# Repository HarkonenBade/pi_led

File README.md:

# pi_led
Raspberry Pi LED Driver

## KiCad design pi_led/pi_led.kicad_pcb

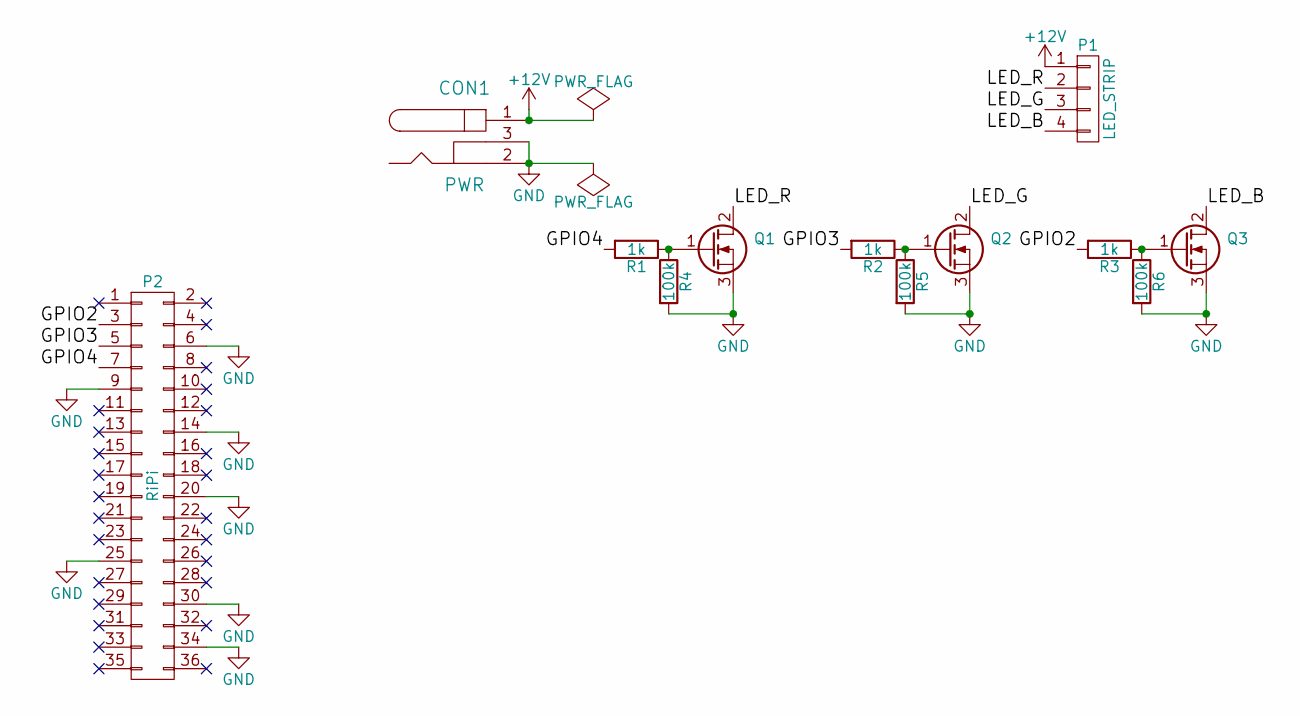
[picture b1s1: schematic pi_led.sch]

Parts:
CON1: PWR; barrel_jack
P1: LED_STRIP; Pin_Header_Angled_1x04
P2: RiPi; Pin_Header_Straight_2x18
Q1, Q2, Q3: STP16NF06L; TO-220_Neutral123_Horizontal; Farnell SC11129
R1, R2, R3: 1k; Resistor_Horizontal_RM10mm
R4, R5, R6: 100k; Resistor_Horizontal_RM10mm

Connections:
+12V: CON1.1, P1.1
/GPIO2: P2.3, R3.2
/GPIO3: P2.5, R2.2
/GPIO4: P2.7, R1.2
/LED_B: P1.4, Q3.2 (D)
/LED_G: P1.3, Q2.2 (D)
/LED_R: P1.2, Q1.2 (D)
GND: CON1.2, CON1.3, P2.6, P2.9, P2.14, P2.20, P2.25, P2.30, P2.34, Q1.3 (S), Q2.3 (S), Q3.3 (S), R4.2, R5.2, R6.2
unnamed: Q1.1 (G), R1.1, R4.1
unnamed: Q2.1 (G), R2.1, R5.1
unnamed: Q3.1 (G), R3.1, R6.1

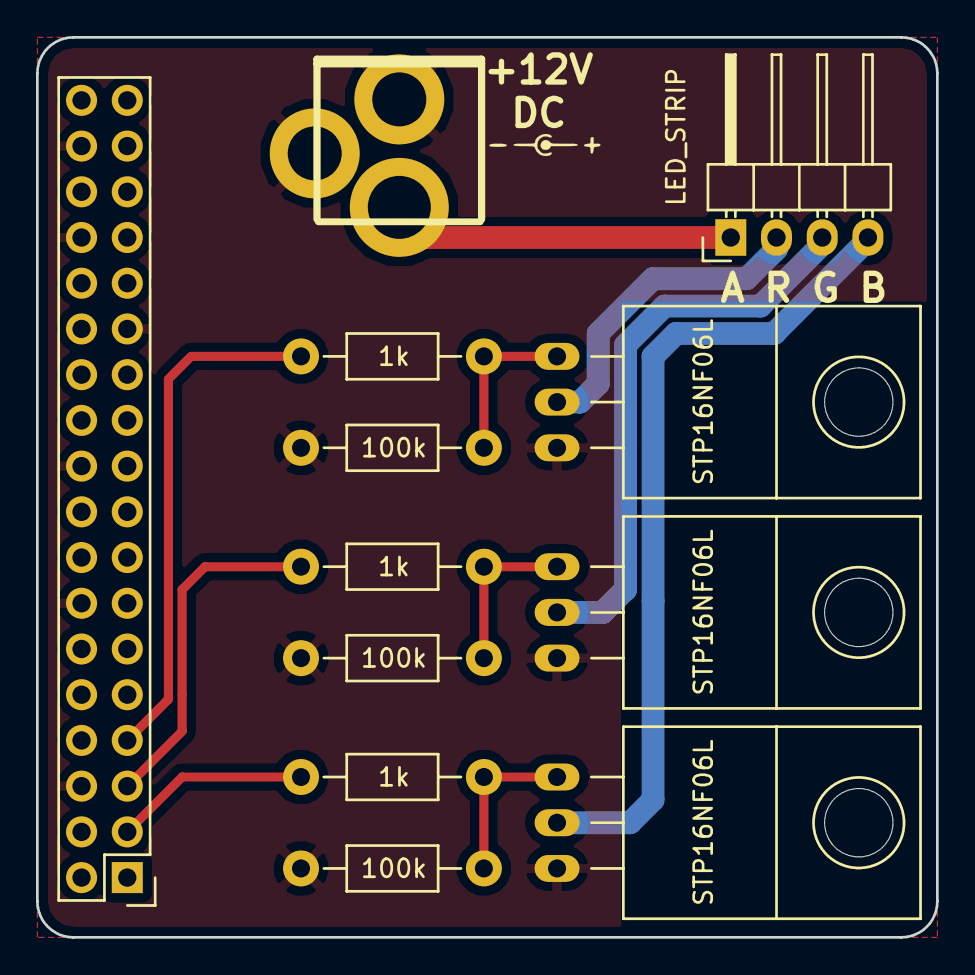
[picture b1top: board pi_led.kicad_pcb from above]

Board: 2 copper layers, 50.0 x 50.0 mm, 12 parts (0 on the bottom side), 11 nets.

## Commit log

2015-08-14 All of schematic and PCB except tidying
2015-08-15 Fix #2, Move labels to silk, General Tidying
2015-08-15 Fix #3: Add centre positive symbol for barrel jack
2015-08-15 Fix #1: Rounded corners and general prettyfying
2015-08-15 Change LED->MOSFET tracks back to 50mil
2015-08-15 Add more GND, add board info
2015-08-15 Added part # to MOSFETs in schematic
2015-08-17 Added front ground net
2015-08-17 Back keepout for MOSFET washers
2015-08-17 Track corner best practices
2015-08-17 Tweak back keepout to be straighter
2015-08-17 Add gerbil files
2015-08-17 Thin out text strokes
2015-08-17 Update gerbils
2015-08-17 Replaced barrel jack part, no slots
    Removed slots from barrel jack part because I don't think Dirty PCBs handles
    plated slots nicely.
    Tweaked LED_B track because clearance was a little close for comfort
    Removed backup file.
